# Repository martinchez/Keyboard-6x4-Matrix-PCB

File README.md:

# Custom Keyboard Matrix PCB Design

This repository contains the files and resources for designing a custom keyboard matrix PCB using KiCad. The project includes detailed schematics, PCB layout, and necessary production files, making it easy to build and customize a keyboard.

## Project Overview

This project aims to design a custom keyboard matrix, including:

- **Schematic Design**: Layout of the electrical connections and components.
- **PCB Layout**: Designing the board with correct placements and routing for each component.
- **Production Files**: Includes Gerber files for manufacturing, and a BOM (Bill of Materials) listing all components required for the build.

## Folder Structure

- `schematics/`: KiCad schematic files for the keyboard matrix design.
- `pcb_layout/`: KiCad PCB layout files.
- `gerber_files/`: Files for PCB production.
- `bom/`: Bill of Materials in CSV format for ordering components.

## Getting Started

To view and edit this project, you will need [KiCad](https://kicad.org/download/) installed on your machine.

1. Clone this repository:
   ```bash
   git clone <repository-url>
   cd <repository-folder>
   ```
2. Open the project in KiCad by loading the `.kicad_pro` file in the root directory.

## Usage

# Modifying the Schematic

To modify the schematic, open the files in the `schematics/` folder and edit as required. Update connections, components, or footprints as needed.

# PCB Layout

The `pcb_layout/` folder contains the board layout, with all necessary routing, component placements, and constraints.

# Generating New Gerber Files

After making changes, generate new Gerber files for production by following these steps in KiCad: 1. Open the PCB Editor. 2. Go to File -> Plot and choose your output options. 3. Save the Gerber files in the `gerber_files/` folder.

# License

This project is licensed under the MIT License - see the [LICENSE](https://martinwainaina.xyz/) file for details.

Let me know if you need further modifications!

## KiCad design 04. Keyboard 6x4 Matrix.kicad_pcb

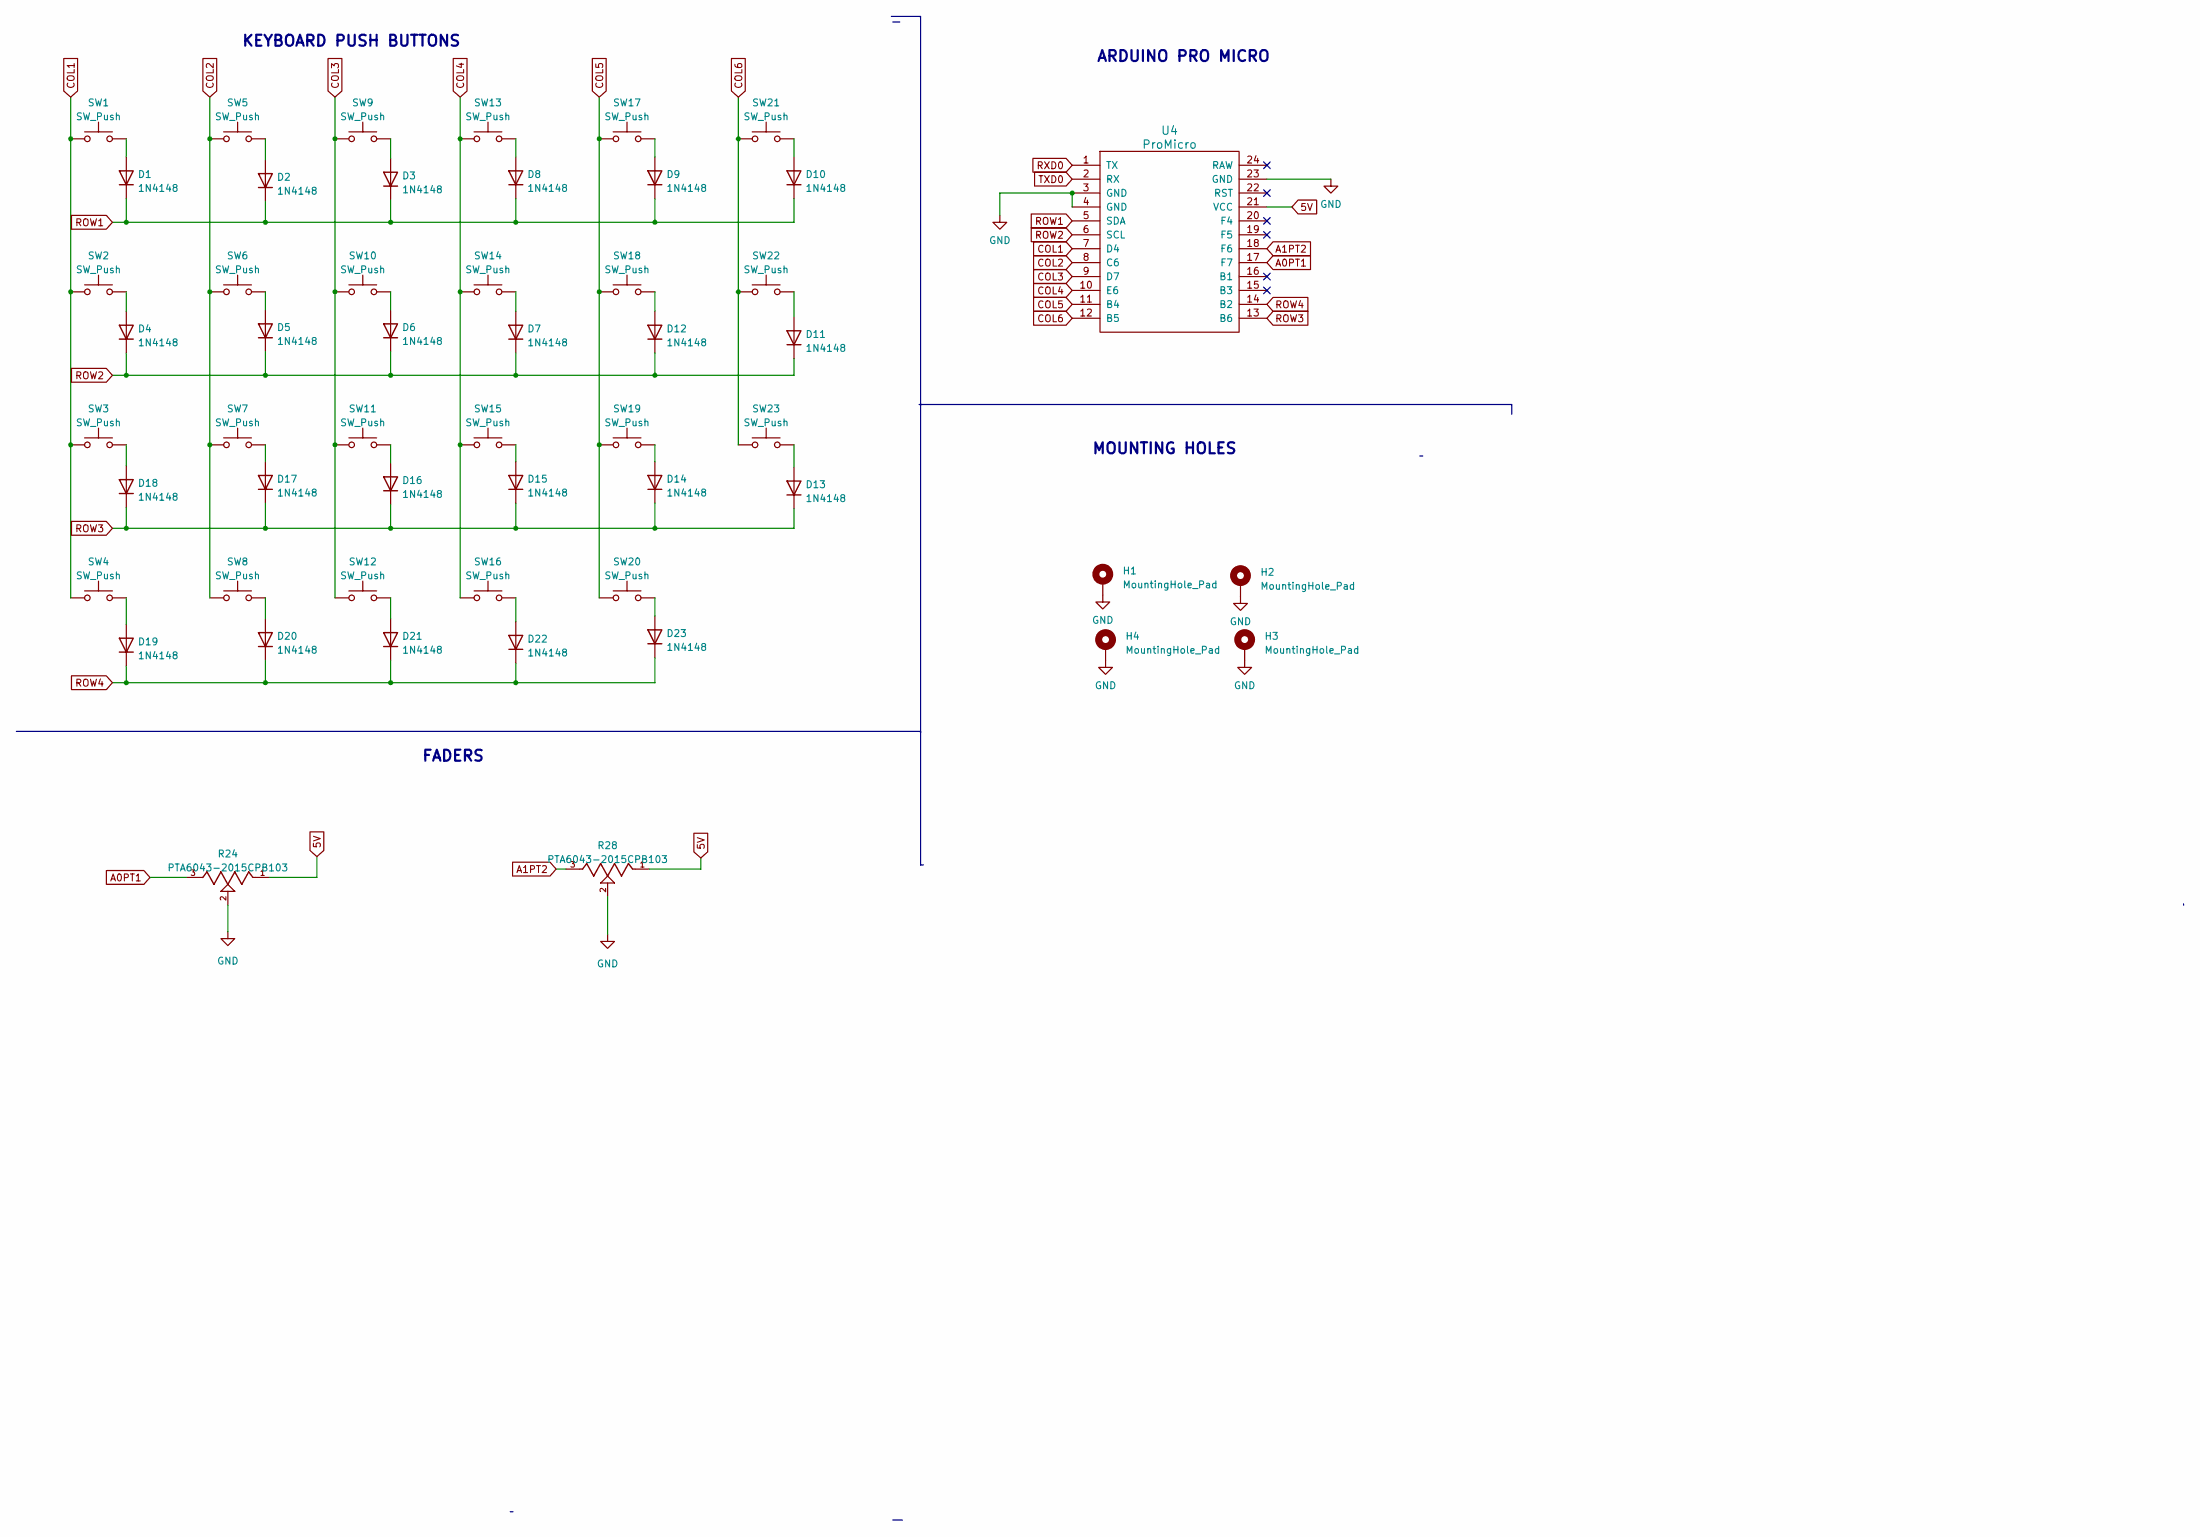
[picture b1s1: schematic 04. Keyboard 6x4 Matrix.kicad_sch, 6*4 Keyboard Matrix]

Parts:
D1, D2, D3, D4, D5, D6, D7, D8, D9, D10, D11, D12, D13, D14, D15, D16, D17, D18, D19, D20, D21, D22, D23: 1N4148; D_0603_1608Metric
H1, H2, H3, H4: MountingHole_Pad; MountingHole_2.7mm_M2.5_Pad_Via
R24, R28: PTA6043-2015CPB103; Potentiometer_Bourns_PTA6043_Single_Slide; PARTREV 04/21
SW1, SW2, SW3, SW4, SW5, SW6, SW7, SW8, SW9, SW10, SW11, SW12, SW13, SW14, SW15, SW16, SW17, SW18, SW19, SW20, SW21, SW22: SW_Push; SW_Cherry_MX_1.00u_PCB
SW23: SW_Push; SW_Cherry_MX_2.00u_Vertical_PCB
U4: ProMicro

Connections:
5V: R24.1, R28.1, U4.21 (VCC)
A0PT1: R24.3, U4.17 (F7)
A1PT2: R28.3, U4.18 (F6)
COL1: SW1.1, SW2.1, SW3.1, SW4.1, U4.7 (D4)
COL2: SW5.1, SW6.1, SW7.1, SW8.1, U4.8 (C6)
COL3: SW9.1, SW10.1, SW11.1, SW12.1, U4.9 (D7)
COL4: SW13.1, SW14.1, SW15.1, SW16.1, U4.10 (E6)
COL5: SW17.1, SW18.1, SW19.1, SW20.1, U4.11 (B4)
COL6: SW21.1, SW22.1, SW23.1, U4.12 (B5)
GND: H1.1, H2.1, H3.1, H4.1, R24.2, R28.2, U4.3 (GND), U4.4 (GND), U4.23 (GND)
unnamed: D1.2 (A), SW1.2
unnamed: D2.2 (A), SW5.2
unnamed: D3.2 (A), SW9.2
unnamed: D4.2 (A), SW2.2
unnamed: D5.2 (A), SW6.2
unnamed: D6.2 (A), SW10.2
unnamed: D7.2 (A), SW14.2
unnamed: D8.2 (A), SW13.2
unnamed: D9.2 (A), SW17.2
unnamed: D10.2 (A), SW21.2
unnamed: D11.2 (A), SW22.2
unnamed: D12.2 (A), SW18.2
unnamed: D13.2 (A), SW23.2
unnamed: D14.2 (A), SW19.2
unnamed: D15.2 (A), SW15.2
unnamed: D16.2 (A), SW11.2
unnamed: D17.2 (A), SW7.2
unnamed: D18.2 (A), SW3.2
unnamed: D19.2 (A), SW4.2
unnamed: D20.2 (A), SW8.2
unnamed: D21.2 (A), SW12.2
unnamed: D22.2 (A), SW16.2
unnamed: D23.2 (A), SW20.2
ROW1: D1.1 (K), D2.1 (K), D3.1 (K), D8.1 (K), D9.1 (K), D10.1 (K), U4.5 (SDA)
ROW2: D4.1 (K), D5.1 (K), D6.1 (K), D7.1 (K), D11.1 (K), D12.1 (K), U4.6 (SCL)
ROW3: D13.1 (K), D14.1 (K), D15.1 (K), D16.1 (K), D17.1 (K), D18.1 (K), U4.13 (B6)
ROW4: D19.1 (K), D20.1 (K), D21.1 (K), D22.1 (K), D23.1 (K), U4.14 (B2)
RXD0: U4.1 (TX)
TXD0: U4.2 (RX)

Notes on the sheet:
KEYBOARD PUSH BUTTONS
MOUNTING HOLES
ARDUINO PRO MICRO
FADERS

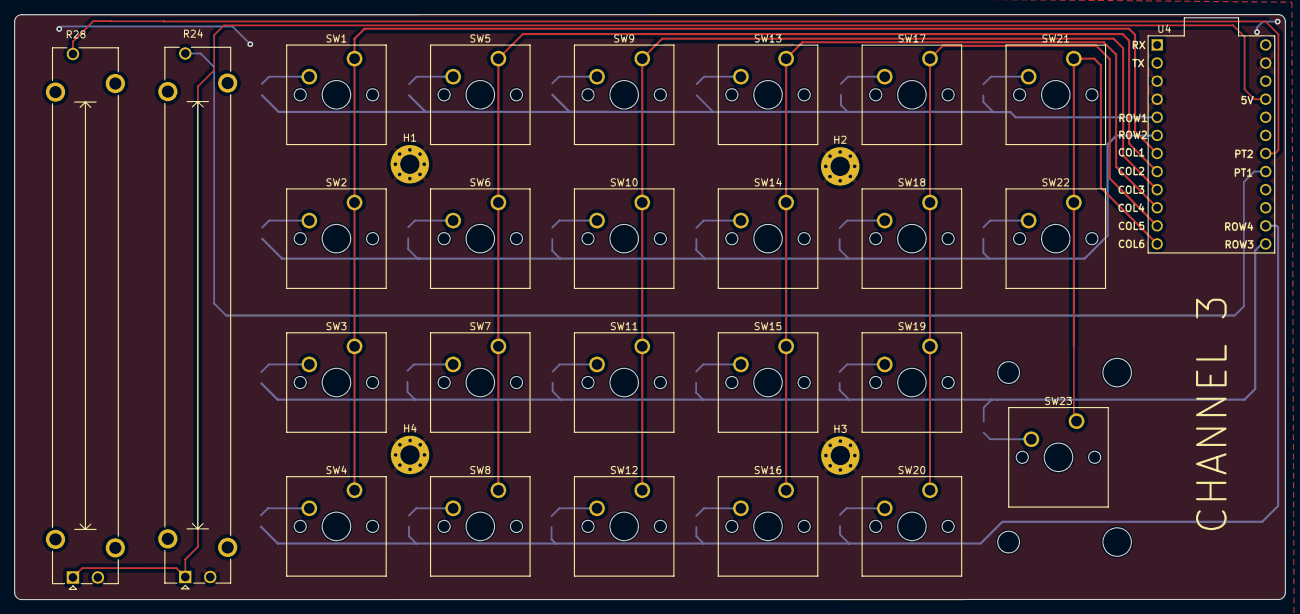
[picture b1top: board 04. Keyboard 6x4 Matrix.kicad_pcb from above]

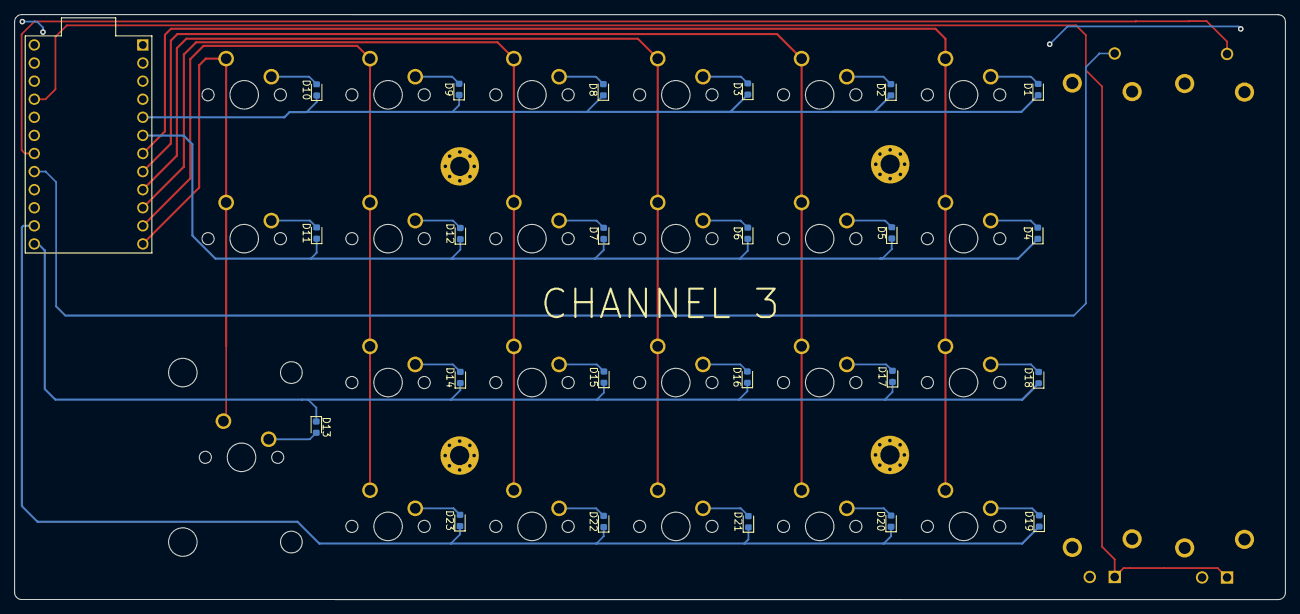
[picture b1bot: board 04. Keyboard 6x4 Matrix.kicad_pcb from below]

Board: 2 copper layers, 178.4 x 82.1 mm, 53 parts (23 on the bottom side), 37 nets.

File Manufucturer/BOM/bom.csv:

"Id";"Designator";"Footprint";"Quantity";"Designation";"Supplier and ref";
1;"SW17,SW14,SW12,SW15,SW1,SW4,SW19,SW6,SW13,SW16,SW18,SW20,SW3,SW5,SW11,SW21,SW8,SW2,SW10,SW9,SW7,SW22";"SW_Cherry_MX_1.00u_PCB";22;"SW_Push";;;
2;"U4";"ProMicro";1;"ProMicro";;;
3;"H2,H3,H1,H4";"MountingHole_2.7mm_M2.5_Pad_Via";4;"MountingHole_Pad";;;
4;"R28,R24";"Potentiometer_Bourns_PTA6043_Single_Slide";2;"PTA6043-2015CPB103";;;
5;"SW23";"SW_Cherry_MX_2.00u_Vertical_PCB";1;"SW_Push";;;

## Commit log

2024-11-11 initial project
2024-11-11 readme
